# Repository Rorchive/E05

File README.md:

<h1 align="center">E05 - Motor Driver</h1>

<p align="center">

</p>

<p align="center">
    <a href="#overview">Overview</a> •
    <a href="#repository-organization">Repository Organization</a> •
    <a href="#releases">Releases</a> •
    <a href="#license">License</a>
</p>

## Overview
This project involves the development of a DC Motor Driver module tailored for the E05 (Transistorized Analog Electronics) course at Inatel. The system is engineered to handle electromechanical switching using a purely analog architecture, providing robust motor control based on a BC547 NPN transistor acting as a driver for a 5V SPDT relay (Songle SRD series). The hardware design incorporates inductive spike protection via a 1N5408 flyback diode, input state stabilization through a push-button with a pull-down network, and real-time visual feedback via an LED indicator.

## Repository Organization

* `docs`: Technical documentation and datasheets.
* `hardware`: Core hardware files.
    * `3D`: 3D models (.step).
    * `Fabrication`: BOM and Gerber files for JLCPCB manufacturing.
    * `PCB`: KiCad schematics and layout design.

## Releases

<table>
  <thead>
    <tr>
      <th>Render</th>
      <th>Board Name</th>
      <th>Status</th>
      <th>Latest Release</th>
      <th>Date</th>
      <th>Datasheet</th>
      <th>BOM</th>
      <th>Ordering Info</th>
    </tr>
  </thead>
  <tbody>
    <tr>
      <td></td>
      <td>Motor Driver v1</td>
      <td>✅ Released</td>
      <td><a href="https://github.com/Rorchive/E05/releases/tag/v1r2">v1r2</a></td>
      <td>2026-06-19</td>
      <td></td>
      <td>No</td>
      <td><a href="hardware/Fabrication/GERBER-Transistor_Driver.zip">GERBER</a> (JLCPCB)</td>
    </tr>
  </tbody>
</table>

## Circuit Operation

Figure (a) illustrates the driver module in its active state with the relay energized (latched) and the LED status indicator turned on while the push-button is pressed, completing the circuit to power the DC motor. Figure (b) depicts the circuit in its default idle state (relay de-energized) with no input applied to the button.

<p align="center">
  
  <br>
  <em>Figure 1: Side-by-side comparison of the mechanical mounting system: (a) Engaged state, (b) Disengaged state.</em>
</p>

## License

This project is licensed under the weakly-reciprocal **[CERN-OHL-W-2.0](LICENSE)** open-hardware license. You are free to modify and distribute these files, provided downstream hardware design modifications remain under the same terms.

---

<br/>

<div align="center">
  
</div>

<div align="center">
<sub>📜 This project is part of <strong><a href="https://github.com/Rorchive">Rorchive</a></strong>, my personal archive of activities and courses developed during my undergraduate studies at <strong>Inatel</strong>.</sub>

  <sub>Built with ❤️ by <a href="https://github.com/RodrigoCAndrade">Rodrigo Andrade</a></sub>
</div>

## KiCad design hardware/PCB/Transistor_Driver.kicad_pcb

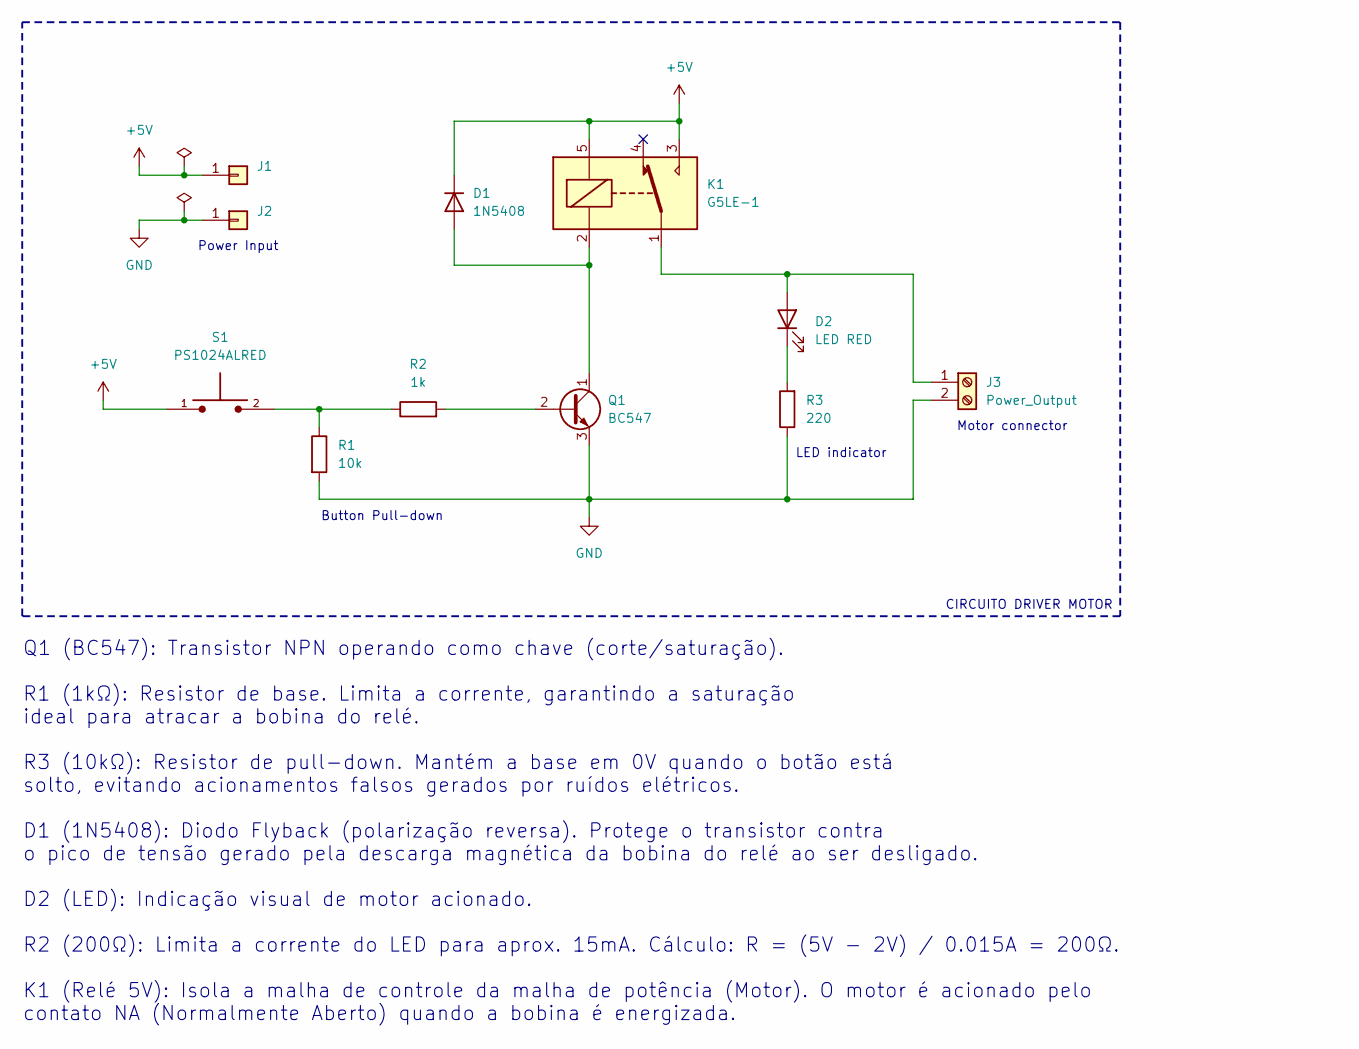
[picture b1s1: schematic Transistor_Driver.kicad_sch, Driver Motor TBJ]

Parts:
D1: 1N5408; D_DO-201AD_P15.24mm_Horizontal
D2: LED RED; LED_D3.0mm_Clear
J1: Conn_5V; PinHeader_1x01_P2.54mm_Vertical
J2: Conn_GND; PinHeader_1x01_P2.54mm_Vertical
J3: Power_Output; TerminalBlock_Phoenix_PT-1,5-2-5.0-H_1x02_P5.00mm_Horizontal
K1: G5LE-1; Relay_SPDT_Omron-G5LE-1
Q1: BC547; TO-92_Inline_Wide
R1: 10k; R_Axial_DIN0207_L6.3mm_D2.5mm_P10.16mm_Horizontal
R2: 1k; R_Axial_DIN0207_L6.3mm_D2.5mm_P10.16mm_Horizontal
R3: 220; R_Axial_DIN0207_L6.3mm_D2.5mm_P10.16mm_Horizontal
S1: PS1024ALRED; SW_PS1024ALRED; PARTREV C

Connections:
+5V: D1.1 (K), J1.1 (Pin_1_1), K1.3, K1.5, S1.1
GND: J2.1 (Pin_1_1), J3.2, Q1.3 (E), R1.2, R3.1
unnamed: D1.2 (A), K1.2, Q1.1 (C)
unnamed: D2.2 (A), J3.1, K1.1
unnamed: D2.1 (K), R3.2
unnamed: Q1.2 (B), R2.2
unnamed: R1.1, R2.1, S1.2

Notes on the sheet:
LED indicator
Power Input
Button Pull-down
Q1 (BC547): Transistor NPN operando como chave (corte/saturação). R1 (1kΩ): Resistor de base. Limita a corrente, garantindo a saturação ideal para atracar a bobina do relé. R3 (10kΩ): Resistor de pull-down. Mantém a base em 0V quando o botão está solto, evitando acionamentos falsos gerados por ruíd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
Motor connector
CIRCUITO DRIVER MOTOR

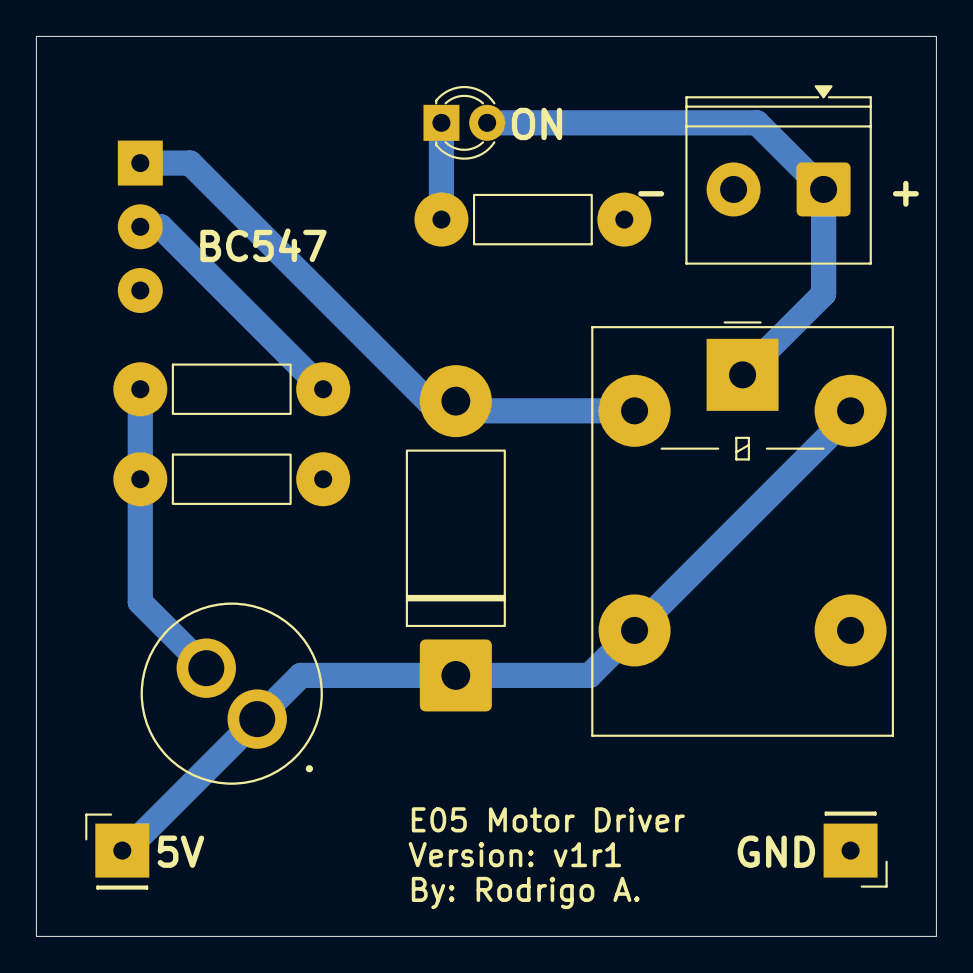
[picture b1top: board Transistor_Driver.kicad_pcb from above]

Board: 2 copper layers, 50.0 x 50.0 mm, 11 parts (0 on the bottom side), 7 nets.

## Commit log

2026-06-17 feat(schematic): add schematic v1
2026-06-18 feat(hardware): add PCB design
2026-06-18 feat(hardware): add teardrops
2026-06-18 feat(hardware): finalize PCB design and refactor repository files
2026-06-19 feat(hardware): release v1r2
